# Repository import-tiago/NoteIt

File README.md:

# NoteIt

**NoteIt** is a datalogger for devices based on UART protocols.

It is powered by rechargeable battery, has micro-SD memory card storage with [FatFs](http://elm-chan.org/fsw/ff/00index_e.html), compatibility with 5V and 3.3V levels, automatic baud rate detector/manual baud rate selection; and, optionally, you can add date, time and temperature to the recorded data.

All settings can be easily configured via the OLED display and rotary encoder.

The content stored on the memory card can be accessed by a computer using a USB type C cable connected directly to the NoteIt, without the needed for an external USB/SD-Card adapter.

|  |  |  |
|--|--|--|

This device was developed to be used in the simplest, carefree and agile way possible: just connect to the target device and know that the data is being saved.

- Don't worry about the file name: the management of files on the SD-Card is done automatically.
- Don't worry about voltage levels: being UART, the data will be registered.
- Don't worry about the datalogger power supply: it has its own power supply and is ultra low consumption, you can use it for weeks without an external source. If you want, you can use an external 5V source via USB cable type C.

## Screens Prototypes Preview

Custom symbols created using [image2cpp](https://javl.github.io/image2cpp/).

| Baud Rate Selection Screen | Log File Settings Screen | Clock and Calendar Adjustment Screen |
|--|--|--|
|  |  | |

## Schematic Preview
<p align="center"></p>

To improve the aesthetics and reliability of the project, all devices (symbol + footprint + 3D model) used in this development belong to my own libraries, which have been tested and validated over time:

## PCB Preview
- 50 mm x 35 mm / 4 layers.
<p align="center"><a href="https://github.com/import-tiago/NoteIt/tree/main/Hardware/1.%20Production"></p>

### Contributing
0. Give this project a :star:
1. Create an issue and describe your idea.
2. [Fork it](https://github.com/import-tiago/NoteIt/fork).
3. Create your feature branch (`git checkout -b my-new-feature`).
4. Commit your changes (`git commit -a -m "Added feature title"`).
5. Publish the branch (`git push origin my-new-feature`).
6. Create a new pull request.
7. Done! :heavy_check_mark:

### License Information
<p xmlns:cc="http://creativecommons.org/ns#" xmlns:dct="http://purl.org/dc/terms/"><a property="dct:title" rel="cc:attributionURL" href="https://github.com/import-tiago/NoteIt">NoteIt</a> by <a rel="cc:attributionURL dct:creator" property="cc:attributionName" href="https://twitter.com/import_tiago">Tiago Silva</a> is licensed under <a href="http://creativecommons.org/licenses/by-nc/4.0/?ref=chooser-v1" target="_blank" rel="license noopener noreferrer" style="display:inline-block;">CC BY-NC 4.0 </a></p>

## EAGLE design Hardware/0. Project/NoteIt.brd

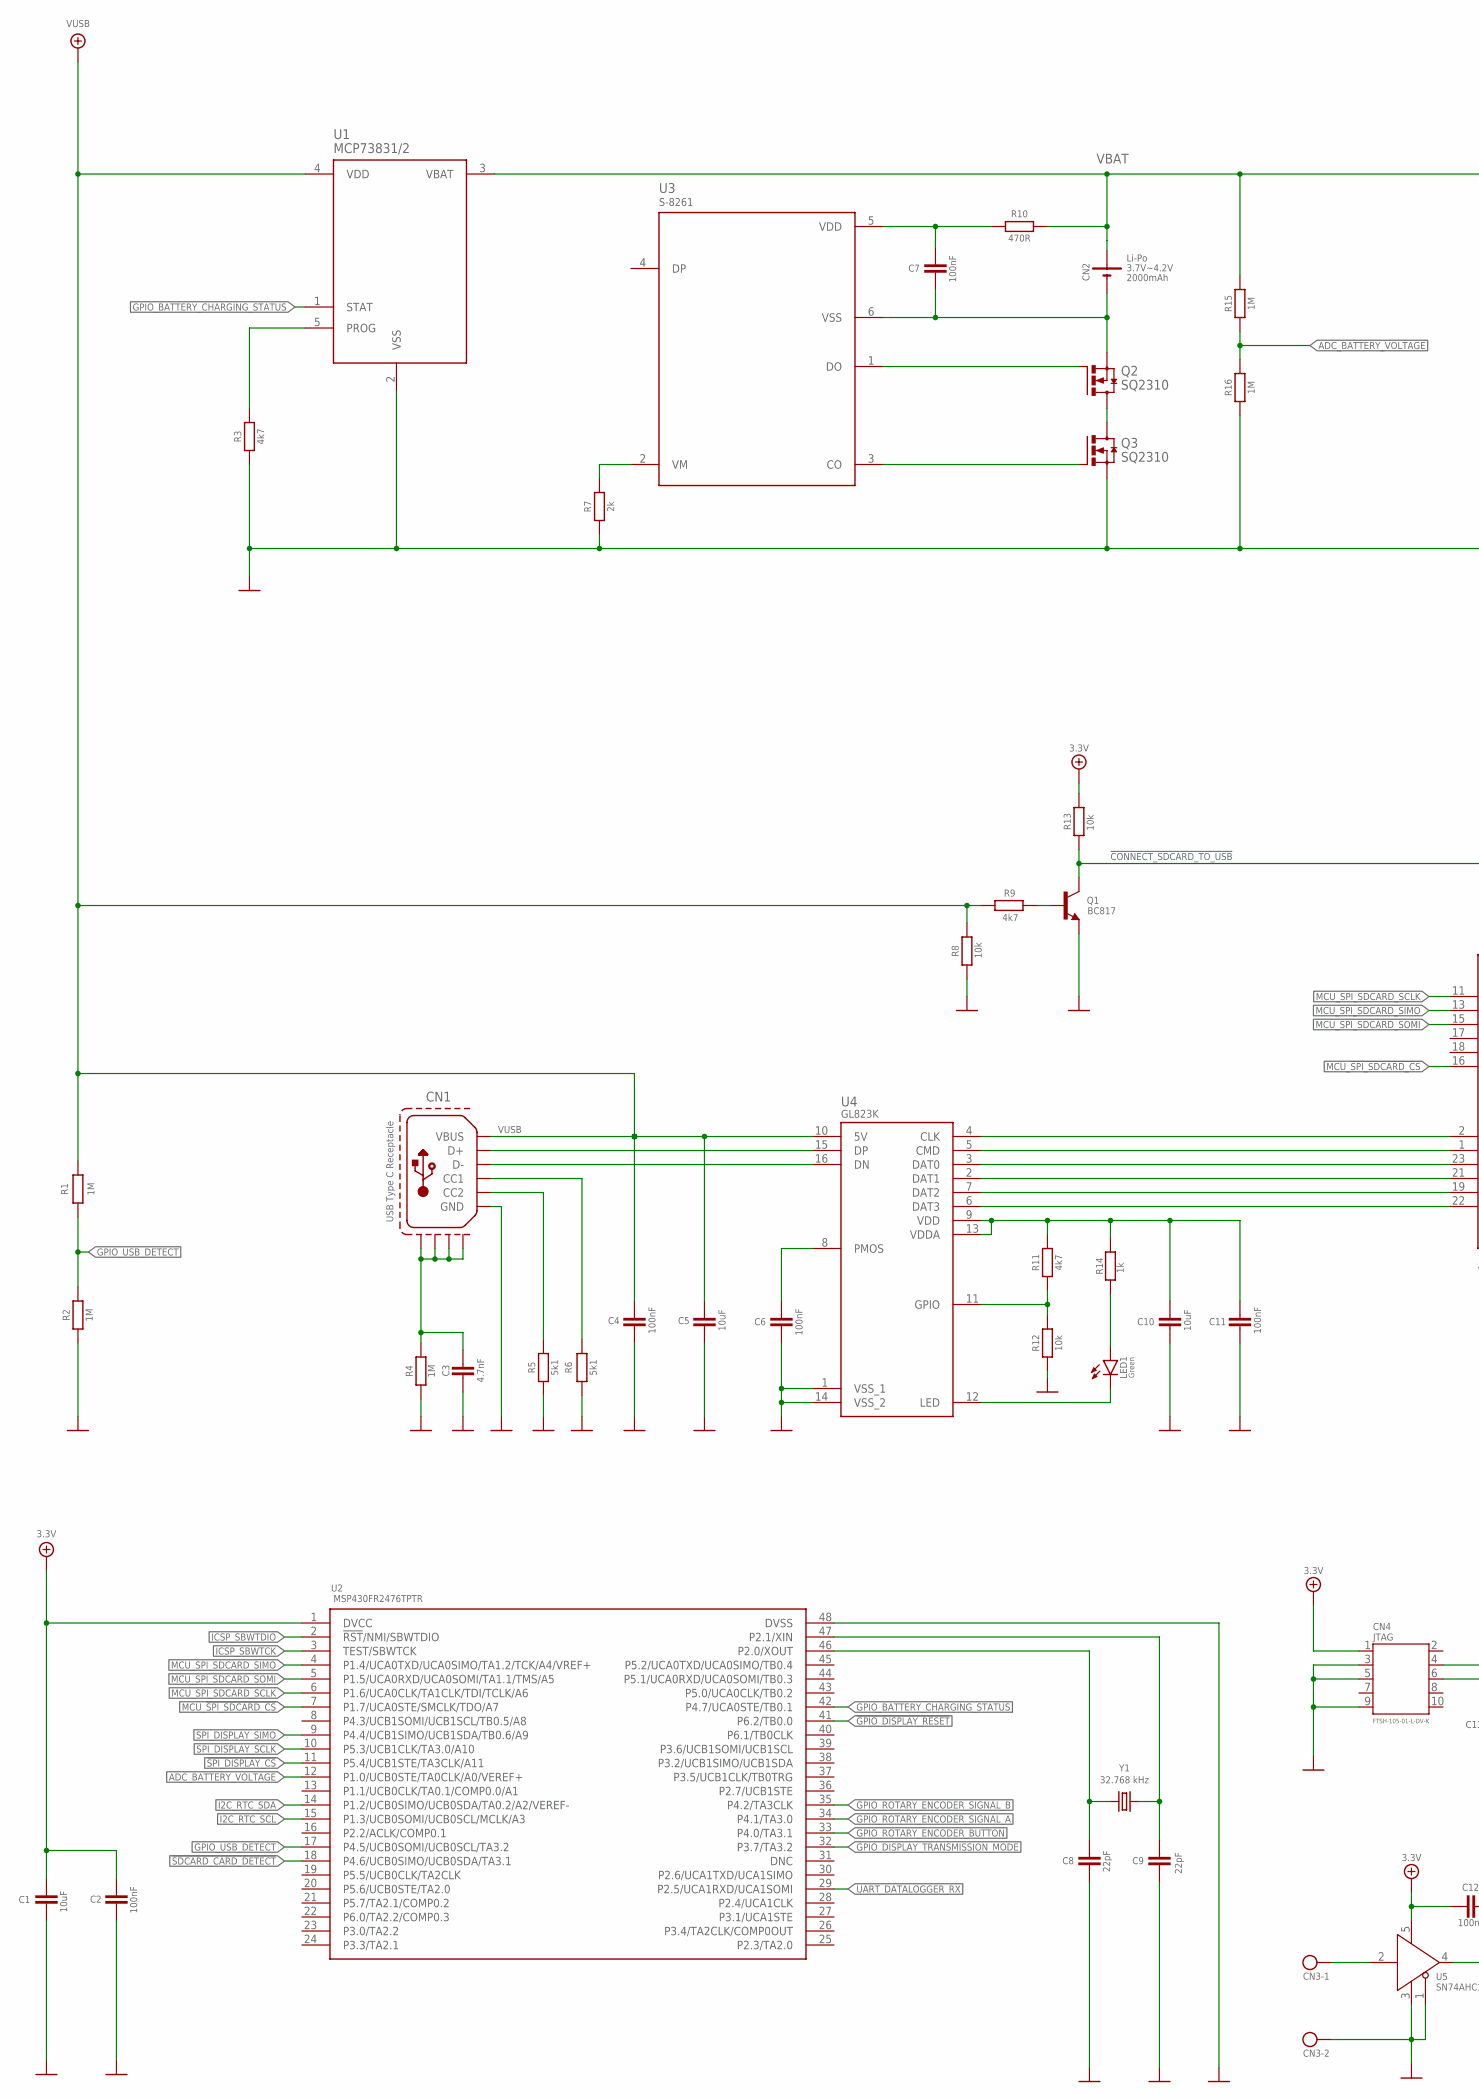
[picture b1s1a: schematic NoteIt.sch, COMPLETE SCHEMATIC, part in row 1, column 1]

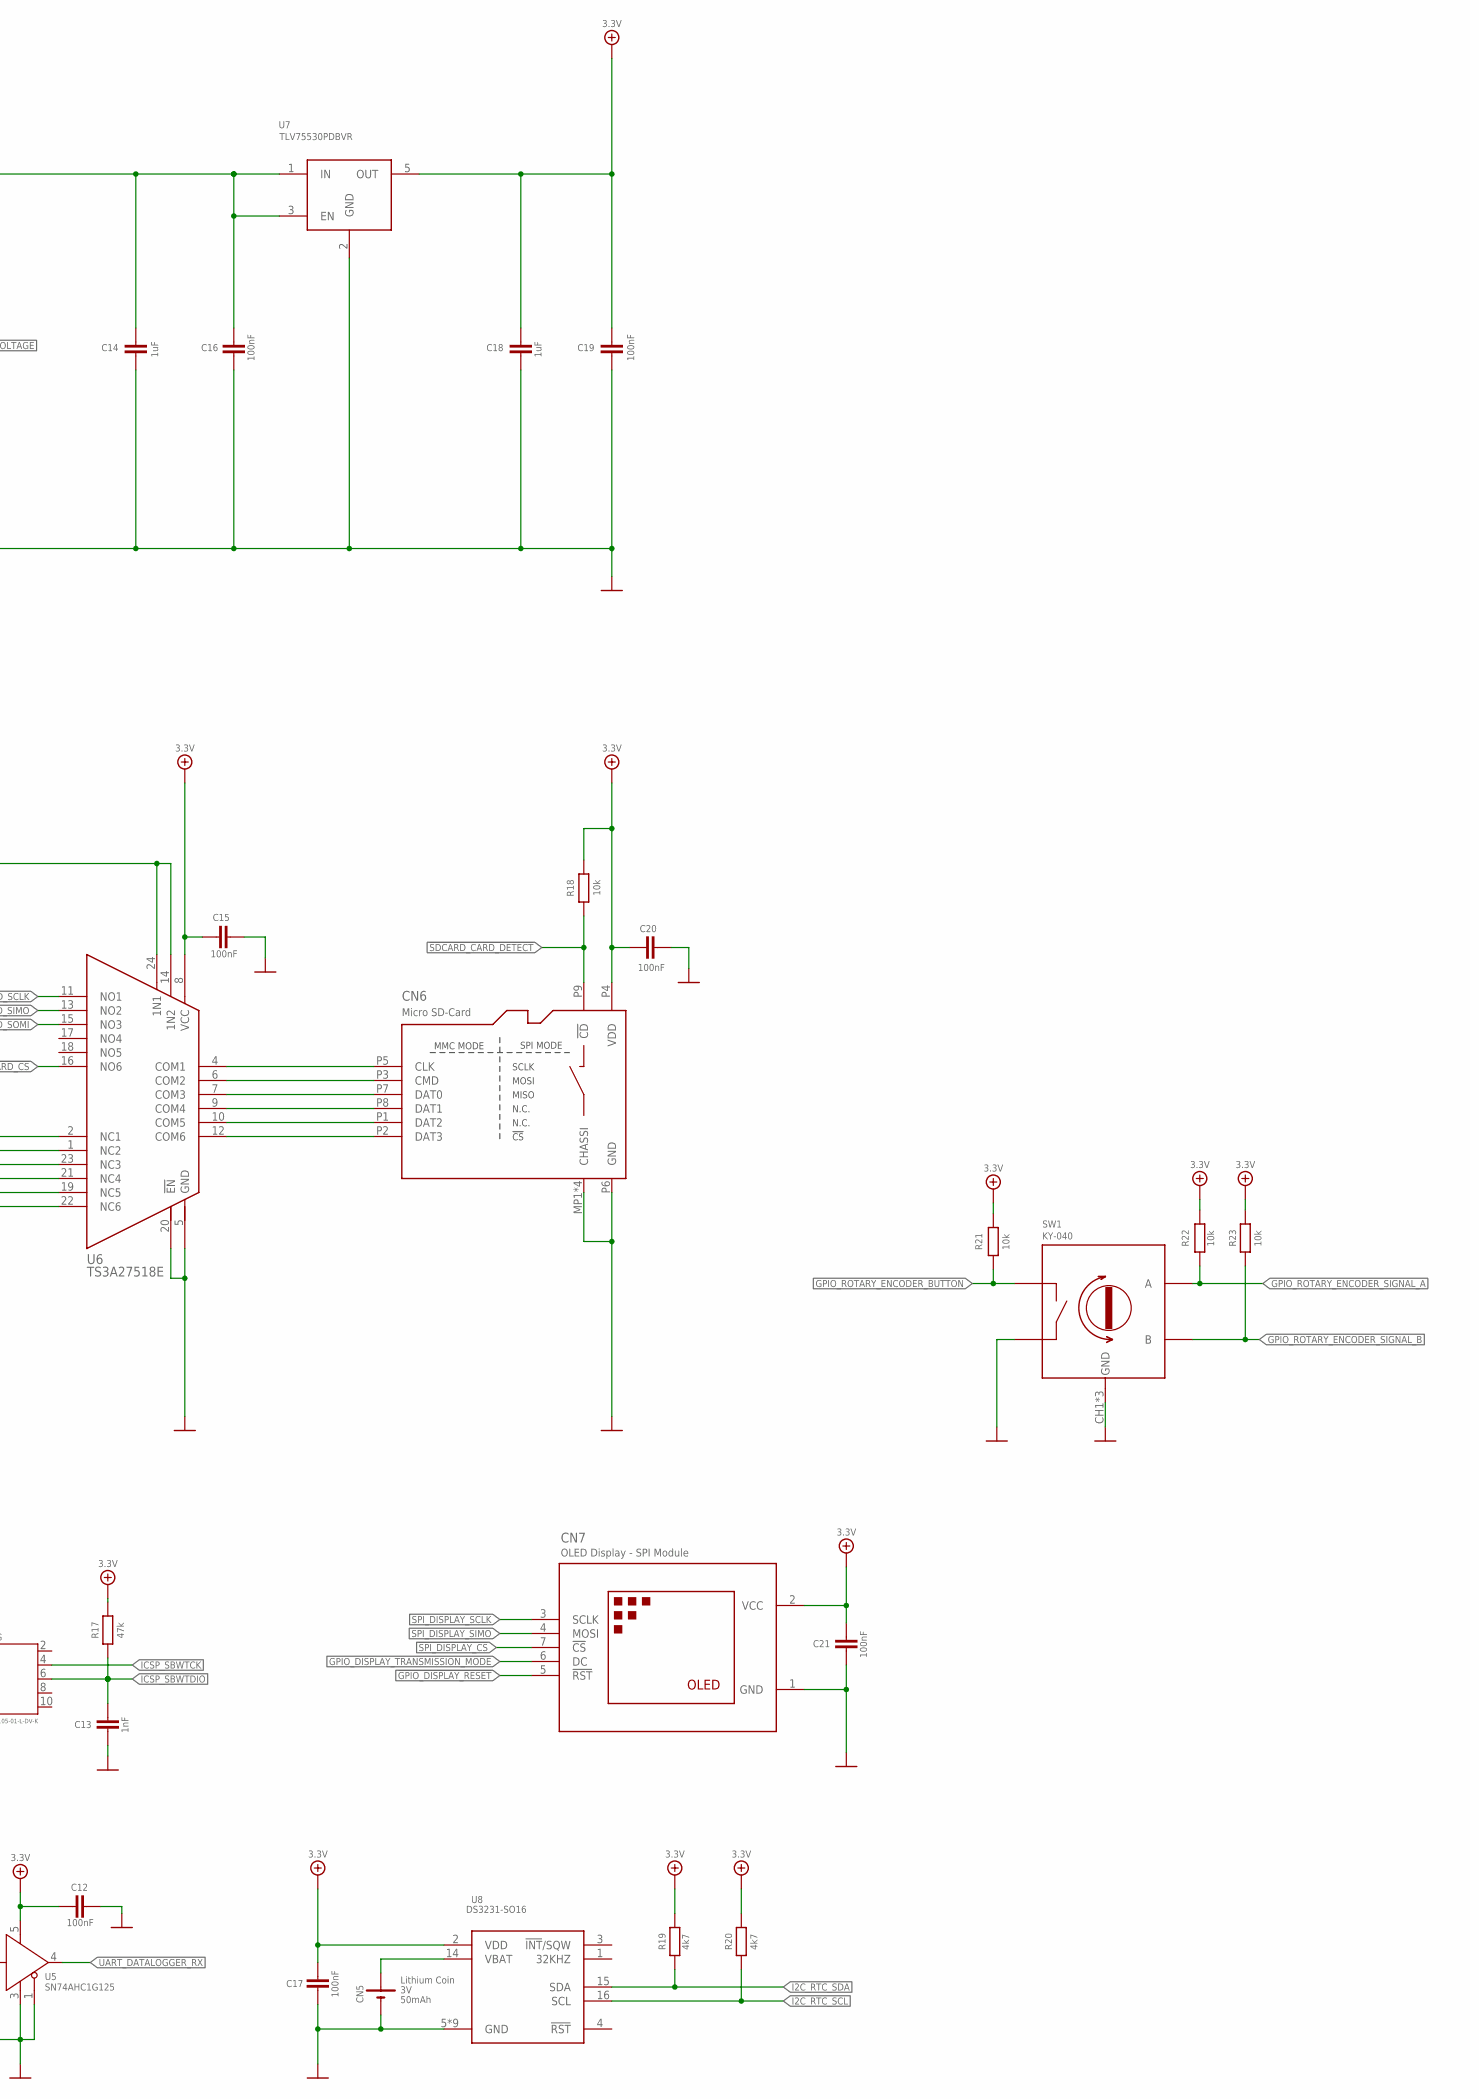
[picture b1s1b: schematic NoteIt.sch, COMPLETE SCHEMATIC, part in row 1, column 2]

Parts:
C1, C5, C10: 10uF; C0603; PARTNO *
C2, C4, C6, C7, C11, C12, C15, C16, C17, C19, C20, C21: 100nF; C0603; PARTNO *
C3: 4.7nF; C0603; PARTNO *
C8, C9: 22pF; C0603; PARTNO *
C13: 1nF; C0603; PARTNO *
C14, C18: 1uF; C0603; PARTNO *
CN1: USB Type C Receptacle; USB-C-16P-2LAYER-PADS
CN2: CELL-JST-PH-2P-H; JST-PH-2P-H; VOLTAGE 3.7V~4.2V
CN3: 2P-BLOCK-3.5MM-2P; BLOCK-3.5MM-2P
CN4: JTAG; JTAG-ARM-10P
CN5: CR-1225; CR1220/1225_HOLDER; PARTNO *
CN6: Micro SD-Card; SD-CARD; PARTNO *
CN7: OLED-MODULE-SPI-NO_HOLES; PIN_HEADER_1X7_NH; PARTNO *
LED1: LED-0603
Q1: BC817; SOT23-3; PARTNO *
Q2, Q3: N-FET-ENHANCEMENT-SQ2310; SOT23-3; PARTNO *
R1, R2, R4, R15, R16: 1M; R0603; PARTNO *
R3, R9, R11, R19, R20: 4k7; R0603; PARTNO *
R5, R6: 5k1; R0603; PARTNO *
R7: 2k; R0603; PARTNO *
R8, R12, R13, R18, R21, R22, R23: 10k; R0603; PARTNO *
R10: 470R; R0603; PARTNO *
R14: 1k; R0603; PARTNO *
R17: 47k; R0603; PARTNO *
SW1: KY-040; PARTNO *
U1: MCP73831/2; SOT-23-5; PARTNO *
U2: MSP430FR2476TPTR; LQFP-48; PARTNO *
U3: S-8261; SOT-23-6; PARTNO *
U4: GL823K; SSOP16; PARTNO *
U5: SN74AHC1G125; SOT-23-5; PARTNO *
U6: TS3A27518E; TSSOP-24; PARTNO *
U7: TLV75530PDBVR; SOT-23-5; PARTNO *
U8: DS3231-SO16; SOIC-16W_(SO16); PARTNO *
Y1: 32.768 kHz; 3.2MM_1.6MM; PARTNO *

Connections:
0V: C1.2, C2.2, C3.1, C4.1, C5.1, C6.1, C8.2, C9.2, C10.1, C11.1, C12.2, C13.2, C14.2, C15.1, C16.2, C17.1, C18.2, C19.2, C20.1, C21.2, CN1.GND, CN1.GND2 (GND), CN3.2, CN4.3 (GND), CN4.5 (GND2), CN4.9 (GND3), CN5.-, CN6.MP1 (CHASSI), CN6.MP2 (CHASSI), CN6.MP3 (CHASSI), CN6.MP4 (CHASSI), CN6.P6 (GND), CN7.1 (GND), Q1.2 (E), Q3.2 (S), R2.1, R3.1, R4.2, R5.2, R6.2, R7.1, R8.2, R12.1, R16.1, SW1.CH1 (GND), SW1.CH2 (GND), SW1.GND, SW1.SW2, U1.2 (VSS), U2.48 (DVSS), U4.1 (VSS_1), U4.14 (VSS_2), U5.1 (!OE), U5.3 (GND), U6.5 (GND), U6.20 (!EN), U7.2 (GND), U8.5 (GND), U8.6 (GND), U8.7 (GND), U8.8 (GND), U8.9 (GND), U8.10 (GND), U8.11 (GND), U8.12 (GND), U8.13 (GND)
3.3V: C1.1, C2.1, C12.1, C15.2, C17.2, C18.1, C19.1, C20.2, C21.1, CN4.1 (VDD), CN6.P4 (VDD), CN7.2 (VCC), R13.2, R17.1, R18.1, R19.1, R20.1, R21.1, R22.1, R23.1, U2.1 (DVCC), U5.5 (VDD), U6.8 (VCC), U7.5 (OUT), U8.2 (VDD)
!CONNECT_SDCARD_TO_USB: Q1.3 (C), R13.1, U6.14 (1N2), U6.24 (1N1)
!GPIO_DISPLAY_RESET: CN7.5 (!RST), U2.41 (P6.2/TB0.0)
!SDCARD_CARD_DETECT!: CN6.P9 (!CD), R18.2, U2.18 (P4.6/UCB0SIMO/UCB0SDA/TA3.1)
!SPI_DISPLAY_CS: CN7.7 (!CS), U2.11 (P5.4/UCB1STE/TA3CLK/A11)
ADC_BATTERY_VOLTAGE: R15.1, R16.2, U2.12 (P1.0/UCB0STE/TA0CLK/A0/VEREF+)
GPIO_BATTERY_CHARGING_STATUS: U1.1 (STAT), U2.42 (P4.7/UCA0STE/TB0.1)
GPIO_DISPLAY_TRANSMISSION_MODE: CN7.6 (DC), U2.32 (P3.7/TA3.2)
GPIO_ROTARY_ENCODER_BUTTON: R21.2, SW1.SW1, U2.33 (P4.0/TA3.1)
GPIO_ROTARY_ENCODER_SIGNAL_A: R22.2, SW1.A, U2.34 (P4.1/TA3.0)
GPIO_ROTARY_ENCODER_SIGNAL_B: R23.2, SW1.B, U2.35 (P4.2/TA3CLK)
GPIO_USB_DETECT: R1.1, R2.2, U2.17 (P4.5/UCB0SOMI/UCB0SCL/TA3.2)
I2C_RTC_SCL: R20.2, U2.15 (P1.3/UCB0SOMI/UCB0SCL/MCLK/A3), U8.16 (SCL)
I2C_RTC_SDA: R19.2, U2.14 (P1.2/UCB0SIMO/UCB0SDA/TA0.2/A2/VEREF-), U8.15 (SDA)
ICSP_SBWTCK: CN4.4 (TCK), U2.3 (TEST/SBWTCK)
ICSP_SBWTDIO: C13.1, CN4.6 (TDO), R17.2, U2.2 (!RST!/NMI/SBWTDIO)
MCU_!SPI_SDCARD_CS: U2.7 (P1.7/UCA0STE/SMCLK/TDO/A7), U6.16 (NO6)
MCU_SPI_SDCARD_SCLK: U2.6 (P1.6/UCA0CLK/TA1CLK/TDI/TCLK/A6), U6.11 (NO1)
MCU_SPI_SDCARD_SIMO: U2.4 (P1.4/UCA0TXD/UCA0SIMO/TA1.2/TCK/A4/VREF+), U6.13 (NO2)
MCU_SPI_SDCARD_SOMI: U2.5 (P1.5/UCA0RXD/UCA0SOMI/TA1.1/TMS/A5), U6.15 (NO3)
unnamed: Q2.1 (G), U3.1 (DO)
unnamed: CN6.P5 (CLK), U6.4 (COM1)
unnamed: Q2.3 (D), Q3.3 (D)
unnamed: CN3.1, U5.2 (IN)
unnamed: LED1.C (K), U4.12 (LED)
unnamed: CN1.B5 (CC2), R5.1
unnamed: CN6.P1 (DAT2), U6.10 (COM5)
unnamed: CN6.P2 (DAT3), U6.12 (COM6)
unnamed: LED1.A, R14.2
unnamed: C3.2, CN1.SHLD1 (S1), CN1.SHLD2 (S2), CN1.SHLD3 (S3), CN1.SHLD4 (S4), R4.1
unnamed: C10.2, C11.2, R11.1, R14.1, U4.9 (VDD), U4.13 (VDDA)
unnamed: R11.2, R12.2, U4.11 (GPIO)
unnamed: C6.2, U4.8 (PMOS)
unnamed: Q1.1 (B), R9.1
unnamed: CN6.P3 (CMD), U6.6 (COM2)
unnamed: CN6.P7 (DAT0), U6.7 (COM3)
unnamed: CN1.A6 (D+), CN1.B6 (D+), U4.15 (DP)
unnamed: CN1.A7 (D-), CN1.B7 (D-), U4.16 (DN)
unnamed: CN1.A5 (CC1), R6.1
unnamed: CN6.P8 (DAT1), U6.9 (COM4)
unnamed: CN5.+, U8.14 (VBAT)
unnamed: R3.2, U1.5 (PROG)
unnamed: Q3.1 (G), U3.3 (CO)
unnamed: R7.2, U3.2 (VM)
unnamed: C7.1, R10.2, U3.5 (VDD)
unnamed: C7.2, CN2.2 (-), Q2.2 (S), U3.6 (VSS)
SPI_DISPLAY_SCLK: CN7.3 (SCLK), U2.10 (P5.3/UCB1CLK/TA3.0/A10)
SPI_DISPLAY_SIMO: CN7.4 (MOSI), U2.9 (P4.4/UCB1SIMO/UCB1SDA/TB0.6/A9)
UART_DATALOGGER_RX: U2.29 (P2.5/UCA1RXD/UCA1SOMI), U5.4 (OUT)
USB_CLK: U4.4 (CLK), U6.2 (NC1)
USB_CMD: U4.5 (CMD), U6.1 (NC2)
USB_DAT0: U4.3 (DAT0), U6.23 (NC3)
USB_DAT1: U4.2 (DAT1), U6.21 (NC4)
USB_DAT2: U4.7 (DAT2), U6.19 (NC5)
USB_DAT3: U4.6 (DAT3), U6.22 (NC6)
VBAT: C14.1, C16.1, CN2.1 (+), R10.1, R15.2, U1.3 (VBAT), U7.1 (IN), U7.3 (EN)
VUSB: C4.2, C5.2, CN1.VBUS1 (VBUS), CN1.VBUS2 (VBUS), R1.2, R8.1, R9.2, U1.4 (VDD), U4.10 (5V)
XTAL_IN: C8.1, U2.46 (P2.0/XOUT), Y1.1
XTAL_OUT: C9.1, U2.47 (P2.1/XIN), Y1.2

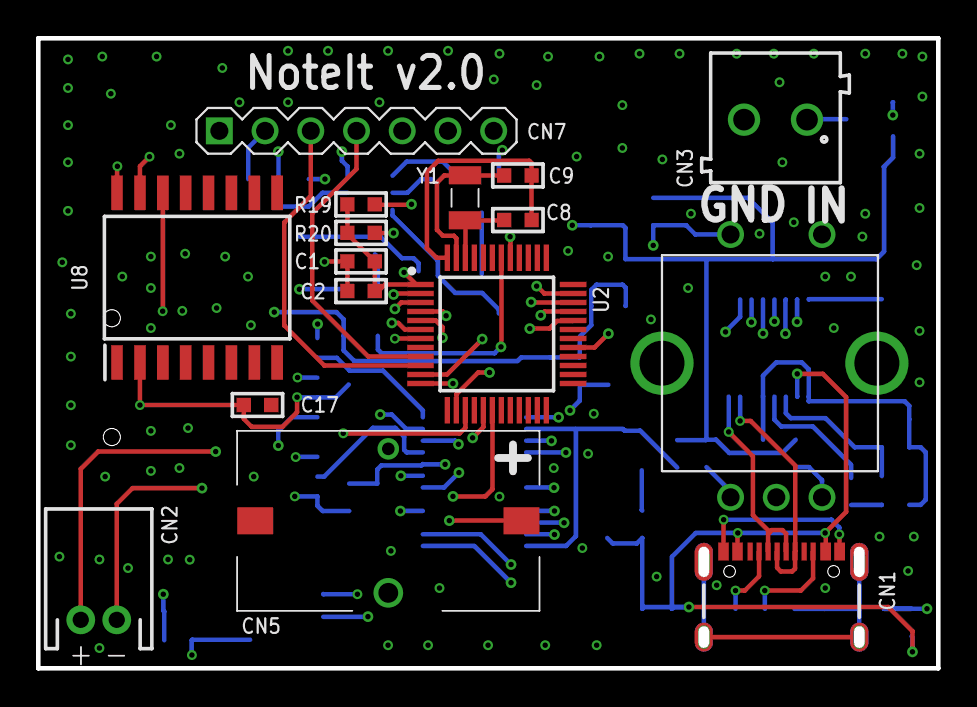
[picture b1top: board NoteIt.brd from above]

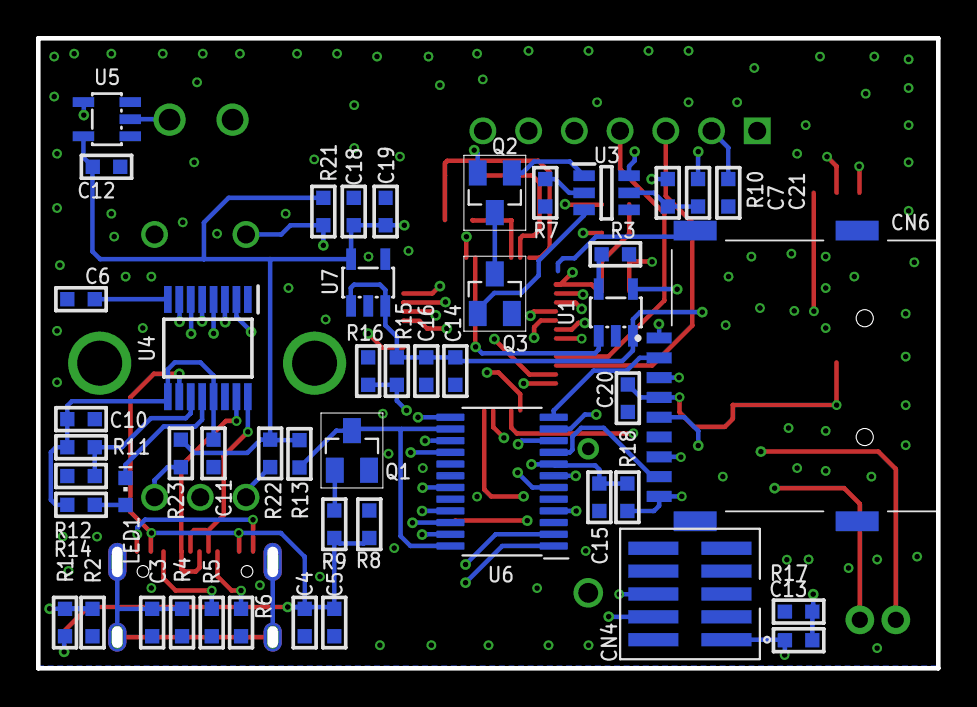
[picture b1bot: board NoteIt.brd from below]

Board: 4 copper layers, 50.0 x 35.0 mm, 65 parts (49 on the bottom side), 60 nets.

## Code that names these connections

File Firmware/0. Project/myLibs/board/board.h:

///////////////////////////////////////////////////////////////////////////////
// Author: Tiago Silva
// E-mail: tiagodepaulasilva@gmail.com
// 2021 - São Paulo, Brazil
///////////////////////////////////////////////////////////////////////////////

#ifndef _BOARDDEFINITIONS_H_
#define _BOARDDEFINITIONS_H_

/********************************************************
 * 				GPIOs
 *	  Micro-SD Card (Card Detect)
 *	       Rotary Encoder
 ********************************************************/
#define GPIO_ROTARY_ENCODER_SWITCH 	BIT0	// P2.0
#define GPIO_ROTARY_ENCODER_SIGNAL_A BIT1	// P2.1
#define GPIO_ROTARY_ENCODER_SIGNAL_B BIT2	// P2.2
#define GPIO_SDCARD_DETECT  			BIT3	// P2.3



/********************************************************
 * 				ADCs
 *		Battery Voltage Monitor
 ********************************************************/
#define ADC_BATTERY_VOLTAGE_PIN  		BIT0 // P1.0



/********************************************************
 * 				UART
 *		External Device (data-log)
 ********************************************************/
#define UART_TX_EXTERNAL_DEVICE_PIN  BIT1 // P1.1



/********************************************************
 * 				SPI
 *		  Micro-SD Card (Read/Write)
 *	 	   OLED Display
 *	    (SETUP on UCB0 bus)
 ********************************************************/
#define SPI_CLK_PIN  					BIT5 // P1.5
#define SPI_MISO_PIN 					BIT6 // P1.6 ('SOMI')
#define SPI_MOSI_PIN 					BIT7 // P1.7 ('SIMO')
#define SPI_SDCARD_CS_PIN 			BIT5 // P2.5
#define SPI_OLED_CS_PIN 				BIT4 // P2.4


#endif  // _BOARDDEFINITIONS_H_

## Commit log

2021-10-26 Basic GPIO test
2021-10-26 Code examples pack added
2021-10-26 Hardware project created
2021-10-26 MCU pins and signals defined
2021-10-26 Datasheet added
2021-10-27 SPI pins changed and I2C pins removed
2021-10-27 Important texts highligthed
2021-10-28 Unused files as a pack
2021-10-29 Migrating from MSP430G2553 to FR4133
2021-11-18 DS3231/I2C working properly
2021-11-18 clear git cache
2021-11-19 I2C communication bug fix + DS3231 Temperature reading
2021-11-19 IDE settings changed
2021-11-19 Relevant info highlighted
2021-11-19 I2C test 1
2021-11-20 I2C + RTC working properly
2021-11-20 MSPMATHLIB added as default math lib
2021-11-20 New libs directories and structure
2021-11-21 IDE minor settings
2021-11-21 Relevant infos highlighted
2021-11-23 eUSCI B1 working properly as SPI (OLED)
2021-11-24 RTC (I2C) + OLED (SPI) working properly
2021-11-24 Heap and stack memory increased to ptintf with float operations
2021-11-25 WIP GPIO_Interrupts
2021-11-26 WIP Rotary Encoder code
2021-11-27 WIP: Rotary Encoder works
2021-11-27 Libs created for rotary encoder and working properly
2021-11-28 New oled lib woriking properly
2021-11-28 I2C clock and date write bug fix
2021-11-29 Screens navigation working properly
2021-11-30 SD Card working properly at eUSCI_A0 (SPI)
2021-11-30 Migrating MCU to FR2476
2021-12-01 Pins names updated to match the schematic signals names
2021-12-01 Signals names added to MCU (matching with firmware)
2021-12-02 USB/MCU <--> Micro-SD Card Interface added
2021-12-03 Relevant indos highlighted
2021-12-03 USB C added + UART Rx (datalogger input) level shifter added
2021-12-04 Refs docs added
2021-12-04 Doc revivion updated
2021-12-05 Added 'Battery_Charging_Status' signal
2021-12-05 Added ICSP docs reference
2021-12-05 Added micro-sd card datasheet
2021-12-06 SD-Card to USB IC (GL823K) package updated
2021-12-07 PCB layout init
2021-12-08 SCH vs BRD conflicts fix
2021-12-09 PCB design WIP
2021-12-09 Standardization footprints from the same package type
2021-12-10 board design wip
2021-12-11 Added external pull ups to rotary encoder
2021-12-12 Relevant infos highligthed
2021-12-12 NoteIt v1.0 release
2021-12-12 Repository readme assets added
2021-12-13 readme updated
2021-12-13 Added schematic v1.0 as PDF file
2021-12-14 Highlighted the JTAG pins used
2021-12-15 Size of images reduced
2021-12-15 Libs dir added to include path
2021-12-16 images converted from png to jpg for best compatibility
2021-12-16 NoteIt v1.1 release (details in commit description)
    - Vias with 0.2mm and 0.4mm diameter drill changed to 0.3mm and 0.6mm diameter drill.
    - The first approach makes the production of PCBs much more expensive (JLCPCB experience).
2021-12-16 NoteIt v1.2 release (details in commit description)
    - All vias changed to 0.3mm drill with 0.6mm diameter.
    - This approach saves money in the production of PCBs (JLCPCB experience) - less tests is necessary.
2021-12-31 Auto build navigation buttons working properly
2022-01-01 remove spaces in image name file
2022-01-01 image added
2022-01-01 minor improvements
2022-01-01 new image added
2022-01-02 I2C last byte transmitted bug fix
2022-01-02 images resized
2022-01-03 OLED fonts arrays reformatted
2022-01-03 Font3216 removed
2022-01-03 home screen current baudrate font resized
2022-01-06 Rotary encoder debounce WIP
2022-01-07 Rotary encoder debounce using ISR working properly
2022-01-16 SPI MUX added
2022-01-18 OLED flicker at multiples redrawings fix (changes SPI clock phase)
2022-01-21 PCB revision WIP
2022-01-21 options in current screen navigation WIP
2022-01-22 Added screen title when in screen navigation mode
2022-01-23 Improved screen navigation by rotary encoder
2022-01-23 Wrong character '6' bug fix
2022-01-23 Baudrate selection in home screen working properly
2022-01-23 Current baudrate center feature improved
2022-01-24 log variables list working properly with scrollbar
2022-01-29 Log Settings Screen working properly with scrollbar + checkbox
2022-01-29 variables abstraction in log screen increased
2022-06-18 Schematic minor improvements and bug fix to pre PCB v3.0 release
    - Fix bug at USB DP and DN.
    - Change all parts to my own libraries.
2022-06-18 Added new aseets
2022-06-18 Folder name changed
2022-06-19 PCB v2.0 release
2022-06-19 Updated to v2.0
2023-07-21 usernames in URLs updated

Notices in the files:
parts and their libraries:
My-RLC: Copyright (C) 2007, Bob Starr
